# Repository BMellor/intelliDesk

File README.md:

intelliDesk
===========

Intelligent LED lighting controller for a lab workspace. Class project for ECE 5780 University of Utah Spring 2014.

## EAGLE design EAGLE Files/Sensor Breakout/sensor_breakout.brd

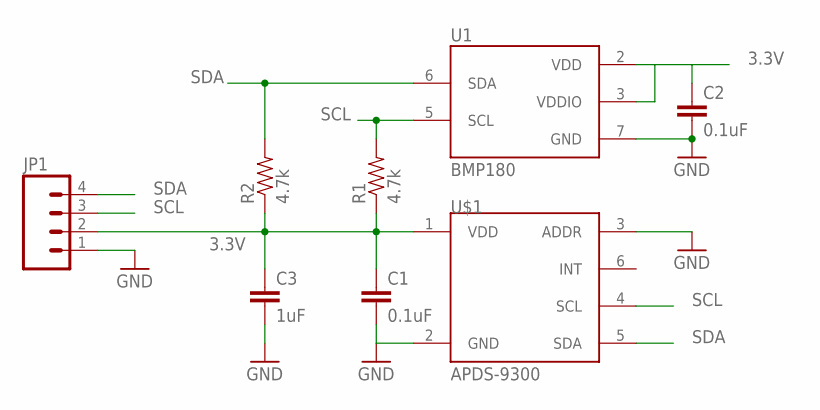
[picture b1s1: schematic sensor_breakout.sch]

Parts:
C1, C2: 0.1uF; 0402-S
C3: 1uF; 0402-S
JP1: M04LOCK; 1X04_LOCK
R1, R2: 4.7k; 0402-S
U1: BMP180
U$1: APDS-9300; CHIPLED

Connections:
3.3V: C1.1, C2.1, C3.1, JP1.2, R1.1, R2.1, U1.2 (VDD), U1.3 (VDDIO), U$1.1 (VDD)
GND: C1.2, C2.2, C3.2, JP1.1, U1.7 (GND), U$1.2 (GND), U$1.3 (ADDR)
SCL: JP1.3, R1.2, U1.5 (SCL), U$1.4 (SCL)
SDA: JP1.4, R2.2, U1.6 (SDA), U$1.5 (SDA)

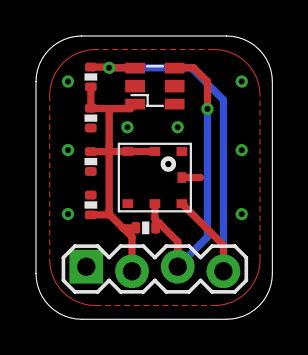
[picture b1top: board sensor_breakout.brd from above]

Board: 2 copper layers, 13.1 x 15.7 mm, 8 parts (0 on the bottom side), 4 nets.

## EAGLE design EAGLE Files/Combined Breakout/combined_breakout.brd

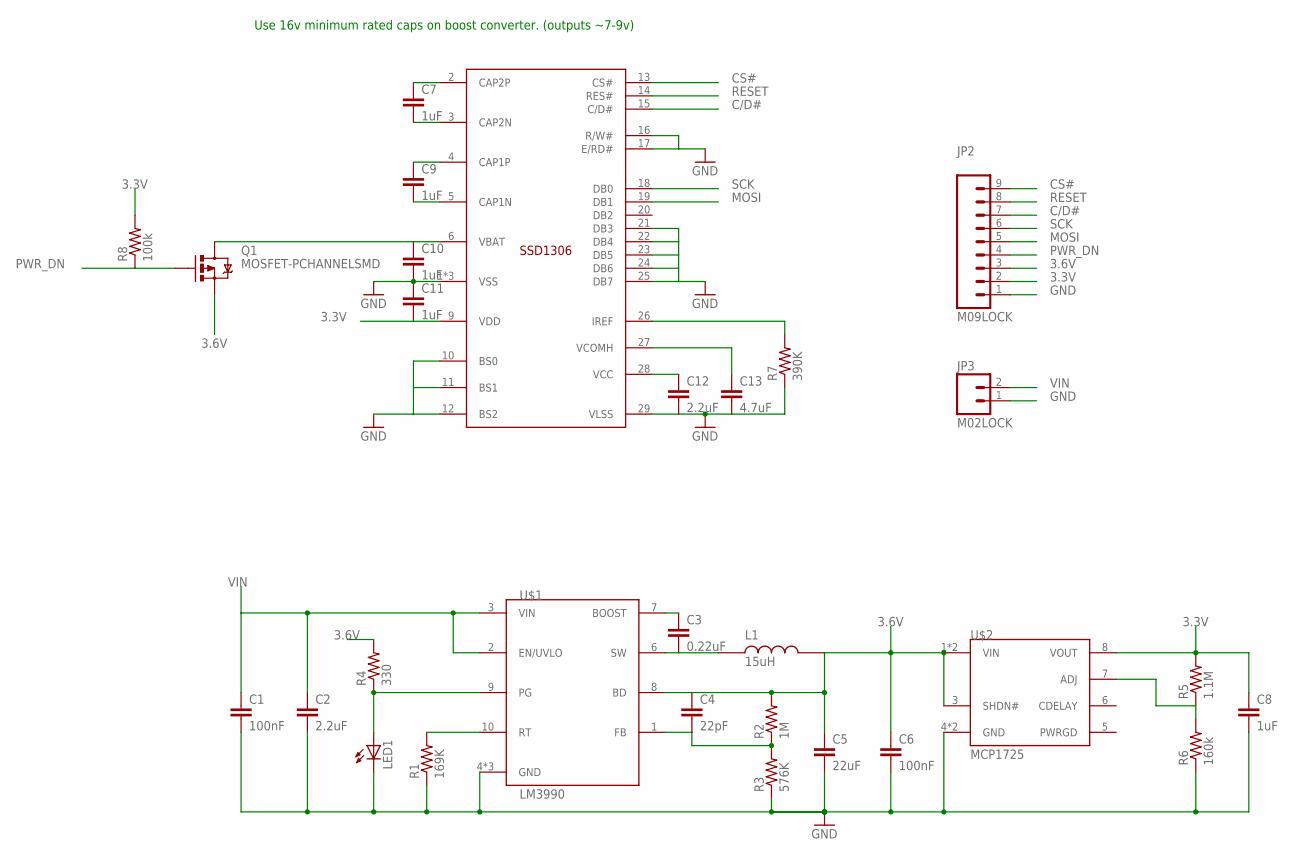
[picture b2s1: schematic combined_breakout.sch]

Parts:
C1, C6: 100nF; 0603-CAP
C2: 2.2uF; 1206
C3: 0.22uF; 0603-CAP
C4: 22pF; 0603-CAP
C5: 22uF; 1206
C7, C9, C10, C11: 1uF; 0402-S
C8: 1uF; 0603-CAP
C12: 2.2uF; 0402-S
C13: 4.7uF; 0402-S
JP2: M09LOCK; 1X09_LOCK
JP3: M02LOCK; 1X02_LOCK
L1: 15uH; NR6028T150M
LED1: LED0603; LED-0603
Q1: MOSFET-PCHANNELSMD; SOT23-3
R1: 169K; 0402-S
R2: 1M; 0402-S
R3: 576K; 0402-S
R4: 330; 0402-S
R5: 1.1M; 0402-S
R6: 160k; 0402-S
R7: 390K; 0402-S
R8: 100k; 0402-S
U$1: LM3990; DD10
U$2: MCP1725; 2X3_DFN
U$3: ER-OLED0.96-2

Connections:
3.3V: C8.1, C11.2, JP2.2, R5.2, R8.2, U$2.8 (VOUT), U$3.9 (VDD)
3.6V: C4.1, C5.1, C6.1, JP2.3, L1.2, Q1.2 (S), R2.2, R4.2, U$1.8 (BD), U$2.1 (VIN), U$2.2 (VIN), U$2.3 (SHDN#)
C/D#: JP2.7, U$3.15 (C/D#)
CS#: JP2.9, U$3.13 (CS#)
FB: C4.2, R2.1, R3.2, U$1.1 (FB)
GND: C1.2, C2.2, C5.2, C6.2, C8.2, C10.2, C11.1, C12.2, C13.2, JP2.1, JP3.1, LED1.C, R1.1, R3.1, R6.1, R7.1, U$1.4 (GND), U$1.5 (GND), U$1.EP\ (GND), U$2.4 (GND), U$2.EP (GND), U$3.1 (VSS), U$3.8 (VSS), U$3.10 (BS0), U$3.11 (BS1), U$3.12 (BS2), U$3.16 (R/W#), U$3.17 (E/RD#), U$3.21 (DB3), U$3.22 (DB4), U$3.23 (DB5), U$3.24 (DB6), U$3.25 (DB7), U$3.29 (VLSS), U$3.30 (VSS)
MOSI: JP2.5, U$3.19 (DB1)
unnamed: C12.1, U$3.28 (VCC)
unnamed: LED1.A, R4.1, U$1.9 (PG)
unnamed: C13.1, U$3.27 (VCOMH)
unnamed: C3.1, U$1.7 (BOOST)
unnamed: R7.2, U$3.26 (IREF)
unnamed: R5.1, R6.2, U$2.7 (ADJ)
unnamed: R1.2, U$1.10 (RT)
unnamed: C9.1, U$3.4 (CAP1P)
unnamed: C9.2, U$3.5 (CAP1N)
unnamed: C7.2, U$3.3 (CAP2N)
unnamed: C7.1, U$3.2 (CAP2P)
unnamed: C10.1, Q1.3 (D), U$3.6 (VBAT)
PWR_DN: JP2.4, Q1.1 (G), R8.1
RESET: JP2.8, U$3.14 (RES#)
SCK: JP2.6, U$3.18 (DB0)
SW: C3.2, L1.1, U$1.6 (SW)
VIN: C1.1, C2.1, JP3.2, U$1.2 (EN/UVLO), U$1.3 (VIN)

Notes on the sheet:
Use 16v minimum rated caps on boost converter. (outputs ~7-9v)

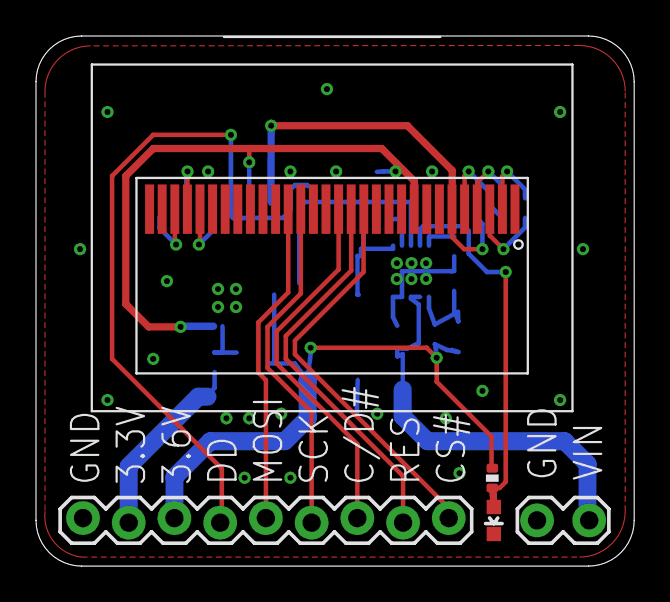
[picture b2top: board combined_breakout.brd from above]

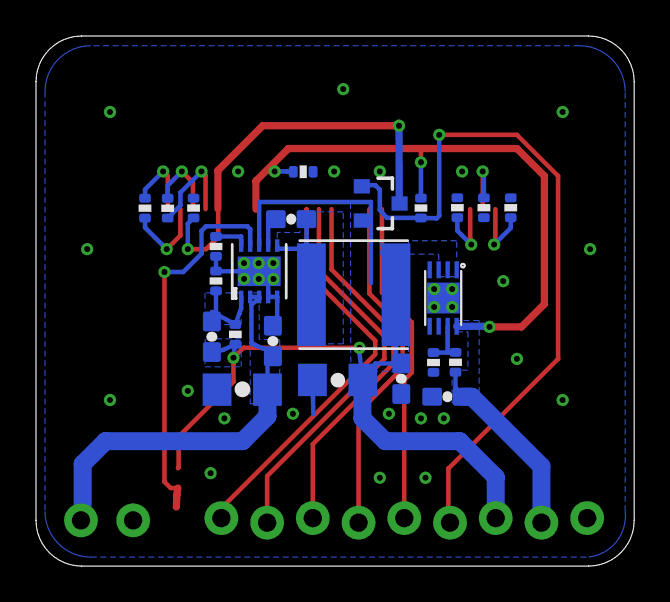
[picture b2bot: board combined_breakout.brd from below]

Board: 2 copper layers, 33.2 x 29.4 mm, 29 parts (24 on the bottom side), 24 nets.

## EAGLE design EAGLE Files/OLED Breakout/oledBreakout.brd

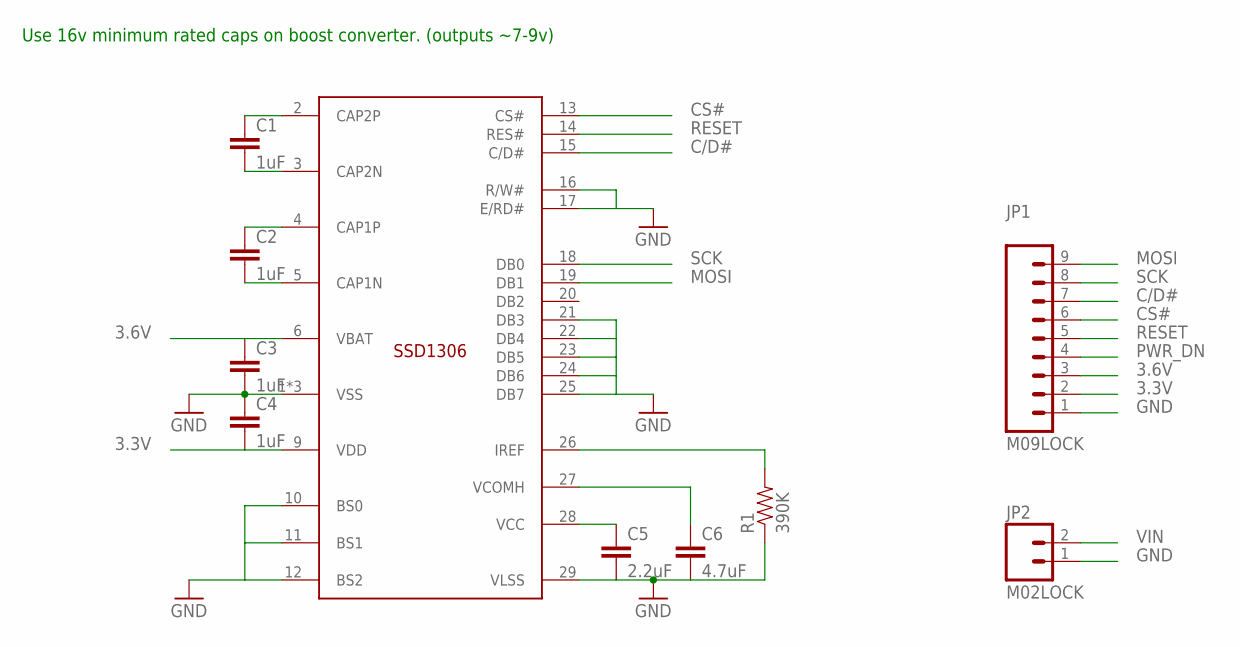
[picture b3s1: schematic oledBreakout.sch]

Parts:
C1, C2, C3, C4: 1uF; 0402-CAP
C5: 2.2uF; 0402-CAP
C6: 4.7uF; 0402-CAP
JP1: M09LOCK; 1X09_LOCK
JP2: M02LOCK; 1X02_LOCK
R1: 390K; 0402-RES
U$1: ER-OLED0.96-2

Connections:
3.3V: C4.2, JP1.2, U$1.9 (VDD)
3.6V: C3.1, JP1.3, U$1.6 (VBAT)
C/D#: JP1.7, U$1.15 (C/D#)
CS#: JP1.6, U$1.13 (CS#)
GND: C3.2, C4.1, C5.2, C6.2, JP1.1, JP2.1, R1.1, U$1.1 (VSS), U$1.8 (VSS), U$1.10 (BS0), U$1.11 (BS1), U$1.12 (BS2), U$1.16 (R/W#), U$1.17 (E/RD#), U$1.21 (DB3), U$1.22 (DB4), U$1.23 (DB5), U$1.24 (DB6), U$1.25 (DB7), U$1.29 (VLSS), U$1.30 (VSS)
MOSI: JP1.9, U$1.19 (DB1)
unnamed: C5.1, U$1.28 (VCC)
unnamed: C6.1, U$1.27 (VCOMH)
unnamed: R1.2, U$1.26 (IREF)
unnamed: C2.2, U$1.5 (CAP1N)
unnamed: C2.1, U$1.4 (CAP1P)
unnamed: C1.2, U$1.3 (CAP2N)
unnamed: C1.1, U$1.2 (CAP2P)
PWR_DN: JP1.4
RESET: JP1.5, U$1.14 (RES#)
SCK: JP1.8, U$1.18 (DB0)
VIN: JP2.2

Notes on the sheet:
Use 16v minimum rated caps on boost converter. (outputs ~7-9v)

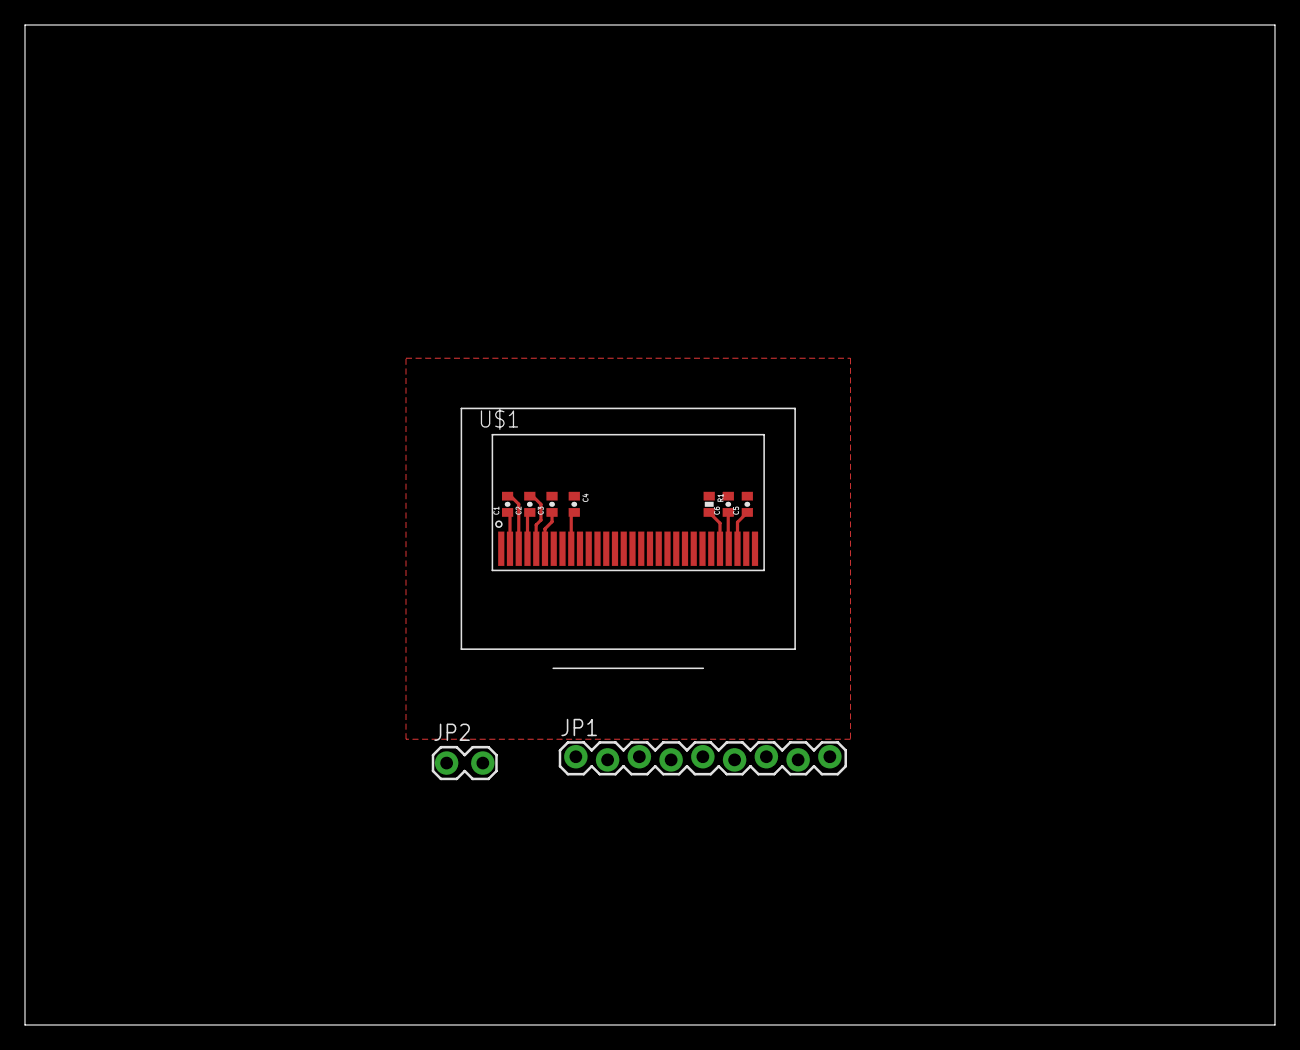
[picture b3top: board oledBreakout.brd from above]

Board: 2 copper layers, 100.0 x 80.0 mm, 10 parts (0 on the bottom side), 15 nets.

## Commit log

2014-03-13 Moved existing design files into Git repo. Added initial design of buck-mode power supply breakout.
2014-03-13 Added polygons to power supply breakout. Text still needs fixing.
2014-03-13 Added polygons to power board. Text needs fixing.
2014-03-14 Added linear reg to power board. Layout ver 1.
2014-03-14 Rerouted for nicer layout on linear supply
2014-03-15 fixed via size and removed most silkscreen on power breakout pcb
2014-03-15 Removed unneeded capacitor on linear supply. Turns out that cap was needed only for power good indicator.
2014-03-15 Added OLED breakout board. (not yet designed) Added linear regulator datasheet. Updated parts library.
2014-03-18 OLED breakout mostly finished. Need to merge with power breakout and decide on header/outputs.
2014-03-19 Combined power/OLED breakouts. Not yet routed completely.
2014-03-20 Routing combined breakout board.
2014-03-21 Finally finished combined breakout board. It's pretty ugly but it will work for prototyping purposes.
2014-03-25 Adjusted spacing on some of the components on the combined breakout board. Removed some silkscreen that was in the way. Checked with freeDFM, sent gerbers off to circuitgraphics!
2014-03-26 Added sensor breakout board. Sent off to CircuitGraphics...
2014-03-26 Forgot to adjust physical outline of the board. Fixed and board is now really uploaded to CircuitGraphics.

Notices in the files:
parts and their libraries:
SparkFun-Connectors: Licensing: CC v3.0 Share-Alike You are welcome to use this library for commercial purposes.
SparkFun-Sensors: Licensing: Creative Commons ShareAlike 4.0 International - https://creativecommons.org/licenses/by-sa/4.0
